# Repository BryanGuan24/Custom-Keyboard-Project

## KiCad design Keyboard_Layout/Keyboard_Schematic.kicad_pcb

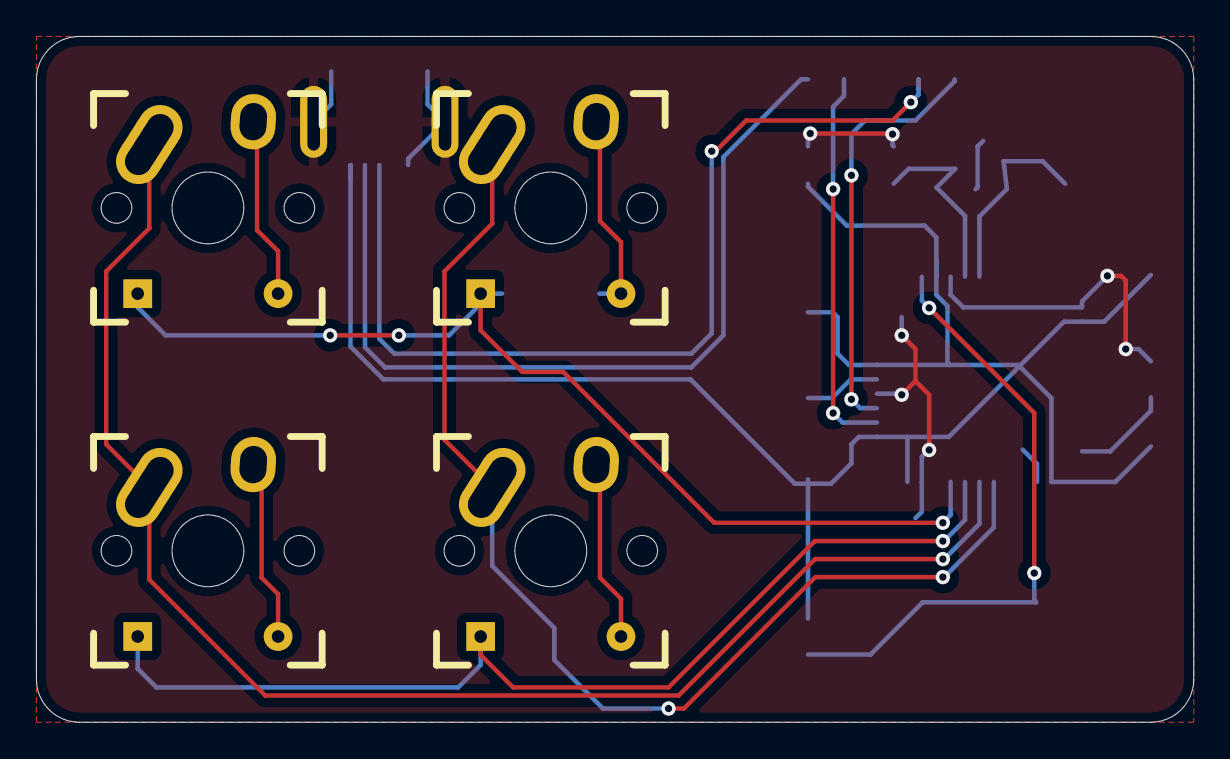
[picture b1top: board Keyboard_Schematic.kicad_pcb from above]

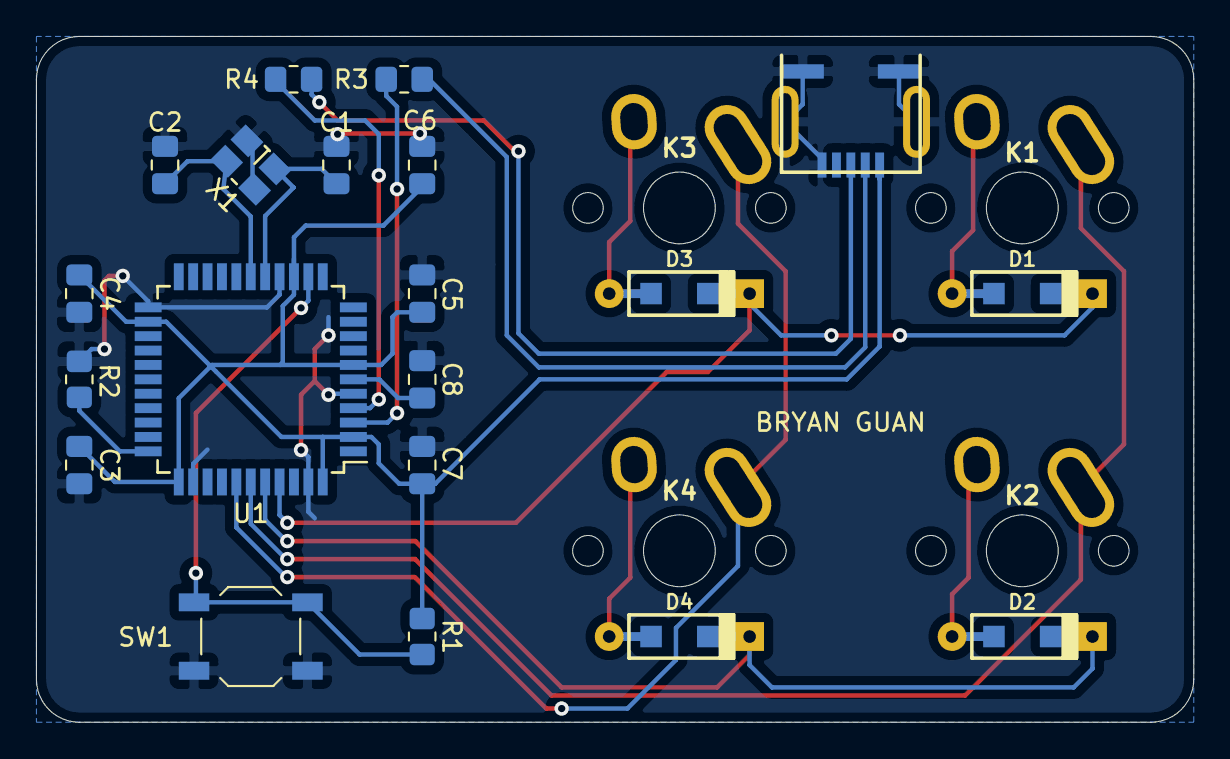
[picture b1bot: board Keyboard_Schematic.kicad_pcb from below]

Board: 2 copper layers, 64.3 x 38.1 mm, 24 parts (20 on the bottom side), 19 nets.

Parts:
C1, C2: 22p; C_0805_2012Metric_Pad1.18x1.45mm_HandSolder
C3, C4, C5, C6: 0.1u; C_0805_2012Metric_Pad1.18x1.45mm_HandSolder
C7: 4.7u; C_0805_2012Metric_Pad1.18x1.45mm_HandSolder
C8: 1u; C_0805_2012Metric_Pad1.18x1.45mm_HandSolder
D1, D2, D3, D4: D; D_SOD123_axial
J1: USB_mini_micro_B; USB_miniB_hirose_5S8
K1, K2, K3, K4: KEYSW; Mx_Alps_100
R1, R2: 10k; R_0805_2012Metric_Pad1.20x1.40mm_HandSolder
R3, R4: 22; R_0805_2012Metric_Pad1.20x1.40mm_HandSolder
SW1: SW_PUSH; SW_SPST_TL3342
U1: ATMEGA32U4; TQFP-44_10x10mm_Pitch0.8mm
X1: XTAL_GND; crystal_FA238-TSX3225

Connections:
/D+: R4.1, U1.4
/D-: R3.1, U1.3
/col0: K1.1, K2.1, U1.39
/col1: K3.1, K4.1, U1.38
/row0: D1.1, D3.1, U1.41
/row1: D2.1, D4.1, U1.40
GND: C1.2, C2.2, C3.2, C4.2, C5.2, C6.2, C7.2, C8.2, J1.5, J1.6, R2.2, SW1.1, U1.5, U1.15, U1.23, U1.35, U1.43, X1.3
unnamed: C1.1, U1.16, X1.1
unnamed: C2.1, U1.17, X1.2
unnamed: C8.1, U1.6
unnamed: D1.2, K1.2
unnamed: D2.2, K2.2
unnamed: D3.2, K3.2
unnamed: D4.2, K4.2
unnamed: J1.2, R3.2
unnamed: J1.3, R4.2
unnamed: R1.2, SW1.2, U1.13
unnamed: R2.1, U1.33
VCC: C3.1, C4.1, C5.1, C6.1, C7.1, J1.1, R1.1, U1.2, U1.7, U1.14, U1.24, U1.34, U1.44

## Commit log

2022-07-16 Cleaning up repository
2022-07-16 Added images of final product
2022-07-16 Added keyboard firmware.
